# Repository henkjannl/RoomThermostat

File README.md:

# Roomthermostat

I wanted to create a room thermostat that can be controlled remotely ('honey, did you remember to switch off the heating?') but which also remains fully operational if internet connectivity is lost. Therefore it can be controlled through Telegram, but also via the hardware unit if WiFi is down. This is also useful since visitors may not want to use Telegram.

This fully (software & mechanics & electronics) open source project is based on an ESP32 microcontroller and the OpenTherm protocol.

The thermostat can be controlled by three touchbuttons on the device or via Telegram. 
In Telegram, an inline keyboard is used which changes depending on the context. This way, the user experience is similar to controlling the device via the hardware. The menu status of each Telegram user is kept in memory, so all users can communicate with the thermostat independently.

### Priorities for the temperature setpoint

The temperature setpoint can be chosen in four different ways, with increasing priority level:
1. The lowest priority level is the **normal week schedule**, which says which day type it is depending on the day of the week. 
    * There are four predefined day types:
        * :house_with_garden: **work from home**: temperature high at wake-up, and low at bed time
        * :office: **work from the office**: temperature high at wake up, low when going out, high when coming home and again low at bed time
        * :dancer: **weekend**, like :house_with_garden: **work from home** but with different wake-up and bed times
        * :palm_tree: **all day away**: temperature low throughout the day
    * The days of the week can be programmed in **settings**. 
    * All times for each type of day type can be modified
    * The low temperature and high temperature can be modified. These are the same temperatures for all day types
2. It is possible to **overrule multiple days** with a different day type, for instance to program multiple days as :dancer: **weekend day** (e.g. holiday at home) or as :palm_tree: **days away** (e.g. holiday away). 
    * The thermostat will be overruled until the number of days expires, or if the **overrule multiple days** function is **switched off** by the user
    * It is also possible to set the number of days to **forever**, for instance if heating is not required during the summer. The **overrule multiple days** can then be **switched off** in autumn.
3. **Today** and **tomorrow** can be overruled by a schedule that is different from the normal schedule.
    * Every night at midnight, **today** is replaced by **tomorrow** and **tomorrow** is switched off
    * Both can be **switched off** or changed by the user
    * For instance: if the holiday starts tomorrow, **multiple days** can be overruled to be :palm_tree: **day away**, after which **today** can be overruled as :dancer: **weekend day**
4. At all times, a **higher or lower temperature** can be manually selected. 
    * When the next programmed timeslot of the lower priority day type dawns, the temperature setting switches back the program of the nearest lower priority
    * It is also possible to choose ```Auto``` from the main menu in Telegram to switch the manual setpoint override off

If the temperature setpoint is manually overruled (priority level 4), it is displayed in red font.

Overruled day icons (priority levels 2 and 3) are surrounded by a red rectangle on the hardware unit. Telegram commands that overrule priority levels 2 and 3 will typically display  day type icons for the next 7 days.

The thermostat can be controlled by three touchbuttons on the device or via Telegram.
In Telegram, an inline keyboard is used which changes depending on the context. This way, the user experience is similar to controlling the device via the hardware. The menu status of each Telegram user is kept in memory, so all users can communicate with the thermostat independently.

## Controlling the thermostat through Telegram
### Main menu in Telegram

After selecting ```/start``` in Telegram, the following message and keyboard are returned:

The temperature in the room or settings of the thermostat can change over time. The display in Telegram is not automatically updated. The ```Status``` button can be used to update the status.

The settings menu has the following options:

### Simple use case in Telegram: going on a short holiday

The scenario is that we are going on a holiday for a few days and we will return on Monday.

To do this, select ```Overrule multiple days...``` in the main menu:

The icons in the next window show that the next two days are currently :office: **work from office**-days, followed by two :dancer: **weekend days** and again some :office: **work from office**-days.

Select :palm_tree:```All day away``` since we will be going on a holiday:

The :palm_tree:```All day away``` scenario means that the setpoint temperature will remain low throughout the day.

Then select ```4 days``` button multiple times in the next menu until the message says there are 5 :palm_tree:**all day away**-days, including Monday, which is the last day that the temperature should remain low:

Next select ```Back to the main menu```:

Now, the current day is also selected as an :palm_tree:**All day away**, with a low temperature setting for the remaining part of the day. To resolve this select ```Overrule today...```:

Choose :dancer:```Weekend day``` so we can pack our bags comfortably:

The remaining **Multiple days** will remain selected, only the current day will be overruled. It is also possible to overrule the next day while the remaining  **multiple days** remain overruled.

Of course it is also possible to do these steps after we leave, without the need to overrule the current day. As we are returning home during the next Saturday, we can also overrule the current day to ensure the house is comfortable upon arrival.

### Switch off the thermostat for a longer period of time

To switch off the thermostat for a longer period of time, for instance during the summer or during a long holiday, proceed as follows:
* Select ```Overrule multiple days...``` in the main menu
* Select :palm_tree: ```All day away```
* Select ```Forever```
* Select ```Back to the main menu...```

The thermostat is now switched off until ```Overrule multiple days``` is ```Switched off```

## Building the device

### Electronic hardware 
The hardware consists of:
* an ESP32 (mh-et-live-minikit-d1)
* an OpenTherm adaptor designed by Ihor Melnyk (DIYless Master OpenTherm Shield - https://diyless.com/product/master-opentherm-shield)
* a 2.4" 320x240 TFT screen (ILI9341)
* a 3D printed housing designed in FreeCad
* up to 4 Dallas DS18B20 temperature sensors
* a 4k7 resistor as pull-up for the Dallas temperature sensors
* 3 touch buttons (stainless steel screws, ISO7380-1, M5 x 16 + nut ISO4032 M5)
* 16 magnets (ø10 x 2.75 mm)
* a PCB designed in KiCad. This is optional, components can also be connected with wires, although it is more work and less reliable

Except for the housing and the OpenTherm interface, everything was ordered at AliExpress. The total bill of materials was about €35. The bill of materials can be found here ```\04 Electrical\Bill of materials.ods```.

### Mechanical hardware

There are two options:
* Connecting electronics via the cross connect PCB - the casing then consists of two panels, see ```03 Mechanical\RoomThermostat.FCStd```
* Connecting electronics via wires - the casing then consists of three panels, see ```03 Mechanical\RoomThermostat with PCB.FCStd```

In case of the PCB, there are two main parts to 3D print, a **front panel** and a **rear panel**. The rear panel can be screwed to the wall. The front panel is clicked on the rear panel through magnets.

Both prints need to be paused in some layer during printing to add round magnets before recommencing the printing.

It is possible to add up to four Dallas temperature sensors on the PCB (but fewer sensors should also work).

There are central ventilation openings on the bottom and top of the device to cool the ESP32 and prevent thermal cross talk between the heat of the ESP32 and the temperature sensors. There are ventilation openings in front of each temperature sensor also to measure the room temperature as accurate as possible.

The sofware has an **adjust sensor offset** feature to add or subtract a value from the measured temperature for calibration. That means that if the temperature measured by the thermostate is different from the actual room temperature, this can be corrected through the hardware buttons or via Telegram. 

### Software preparation
It is required to make a specific Telegram bot account for the thermostat. There are many sources explaining how a new Telegram bot can be created, such as in this [Random Nerd Tutorials Telegram example](https://randomnerdtutorials.com/telegram-control-esp32-esp8266-nodemcu-outputs/).

One ChatID can be provided to which the roomthermostat sends a message upon startup. This is useful to be aware that the thermostat was reset, due to a software bug or power outage.

In order to use the software, the user must first:
* make a copy of `template.jsn` (located in the `..\RoomThermoStat\05 Software\Roomthermostat\data` folder)
* rename the copy `config.jsn` 
* fill in details of one or more WiFi routers, including the timezone in which each router is located (`lon` and `lat` are currently not used)
* upload the data to SPIFFS using the ESP32 sketch upload data tool
* copy `User_Setup.h` and `User_Setup_Select.h` to the `..\Arduino\libraries\TFT_eSPI` folder (perhaps good to backup the existing versions)

The format of the `config.json` file is as follows:

```JSON
{
    "AccessPoints": [
        { "SSID": "SSIDOfWifi1", "password": "PasswordOfWifi1", "timezone" : "Europe/Amsterdam" },
        { "SSID": "SSIDOfWifi2", "password": "PasswordOfWifi2", "timezone" : "Europe/Amsterdam" }
    ],
    "BotName"     : "Name of the bot",
    "BotUsername" : "Username of the bot",
    "BotToken"    : "##########:XXXXXXXXXXXXXXXXXXXXXXXX",
    "ChatID"      : "########"
}
```

Note that there is a `config.json` and a The format of the `config_test.jsn`. The `config_test.jsn` is for test purposes, with a different bot token. It can be used for test purposes while the main thermostat bot remains accessible. To use the test bot, specify ```#define USE_TESTBOT true``` in `Roomthermostat.ino`.

Next it is necessary to upload the data folder to the ESP32 using `Tools` > `ESP32 Sketch Data Upload` in the Arduino IDE (see how this works at [Random Nerd Tutorials Telegram](https://randomnerdtutorials.com/install-esp32-filesystem-uploader-arduino-ide/).

Also, a number of libraries must be installed in Arduino:
* `ArduinoJSON` by Benoît Blanchon - https://arduinojson.org/
* `DallasTemperature` by Miles Burton - https://github.com/milesburton/Arduino-Temperature-Control-Library
* `JPEGDecoder` by Bodmer - https://github.com/Bodmer/JPEGDecoder
* `OpenTherm` by Ihor Melnyk - https://github.com/ihormelnyk/opentherm_library
* `TFT_eSPI` by Bodmer - https://github.com/Bodmer/TFT_eSPI
* `UniversalTelegram` by Brian Lough - https://github.com/witnessmenow/Universal-Arduino-Telegram-Bot

Big shout out to everyone for creating and maintaining these beautiful pieces of work!

## Software internals

### Overview of processes
| File               | Module                                                       |
|--------------------|--------------------------------------------------------------|
| Roomthermostat.ino | Initialization and main loop                                 |
| a_constants.h      | Defines, constants, data types                               |
| b_interfaces.h     | Queues and structs that connect the subsystems               |
| c_logger.h         | Datalogging (to be implemented)                              |
| d_keyboard.h       | Keyboard                                                     |
| e_menu.h           | Menu of hardware unit                                        |
| f_telegram.h       | Handler for Telegram messages                                |
| g_controller.h     | Temperature controller, including PID controller and program |
| h_temperature.h    | Temperature measurement and communication with boiler        |
| i_wifi_time.h      | Wifi controller and real time clock                          |
| j_jpeg.h           | Library to display jpeg images                               |
| k_display.h        | Display of the hardware unit                                 |
| l_backlight.h      | Backlight                                                    |

<br><br>

## Flow of events and messages

Initially, FreeRTOS was envisaged to handle all different processes. However, I did not (yet) get this working together with the OpenTherm library, which is very time critical. It is only possible to debug this with the live boiler attached,  which is a little barrier. Now, all processes are handled sequentially by the main loop.

It also appears that the SPI bus that communicates with the display does not work well while the capacitive touch button routine is called. Every time the display updates, the `touchRead()` is temporarily disabled.

The touch buttons are also disabled while OpenTherm communicates with the boiler.

<br>
The flow of events and messages is as follows:
<br>

* On the left hand side, the events that trigger activities are listed
* The circles represent code
* The arrows between the circles represent messages that are sent over the queues

### User presses key
* the ISR is running at about 30 Hz and is kept a small as possible. The capacitive sensors sometimes give a spike which only lasts one clock tick. Therefor, a key press is only considered valid if the key remains pressed for 2 subsequent samples. The ISR of the keyboard only sends a message to the menu, containing the key that was pressed. Subsequent actions are then carried out by the menu and other modules
* The capacitive sensor does not work well together with the SPI bus of the display, resulting in a crash of the microcontroller. Also, the keyboard ISR can interfere with the timing of the OpenThrem protocol. Therefore, polling the capacitive sensors is disabled during display or OpenTherm communication 
* the Backlight is controlled by the Display. In some cases, a button press does not result in a command to the controller (e.g., pressing the 'up'-button while the top menu item was already selected). In these cases, the backlight should also switch on. Therefore, the menu always sends a `cmdBacklightOn` command directly to the Backlight
* Telegram can take a few seconds to return. To improve responsivity of the keyboard, Telegram is temporarily disabled while the user is interacting with the keyboard. Telegram will be re-enabled as soon as the blacklight switches off.
* the first key press is only used to switch on the backlight. If the backlight is off while a key is pressed, the key is ignored and the backlight is woken up

### User enters a command in Telegram
* the status of the Telegram menu is stored independently for each individual ChatID, so each user can interact with Telegram independently of the other Telegram users and of the hardware unit
* some commands change the status of the controller (e.g., change a wake up time may cause a different setpoint for the boiler), others do not (e.g., moving to another screen in Telegram)
* only commands that change the status of the controller are sent to the controller, the other commands are directly forwarded to the Telegram queue that handles sending a response to the chat
* if the controller receives the command, it causes an update of the display which in turn switches on the backlight. This way, people in the room may notice that the setpoint was potentially changed and may act accordingly
* after the controller completes the action, the command is forwarded to the Telegram queue that returns the response to the user

### The timer for temperature measurement expires
* after the temperature is measured, the controller gets the chance to change the boiler setpoint, and a display update is triggered. This is done via a  `cmdSilentUpdate` command, which does not trigger the backlight: the change is only visible to the user if the backlight was already switched on

### The timer for the boiler expires
* as the timer expires, the controller is called to update the boiler setpoint
* the controller then forwards the `cmdBoilerSending` command to the screen which changes the boiler icon
* then, the screen again forwards the command to the temperature queue which triggers actual communication with the boiler
* finally, a `cmdSilentUpdate` command restores the boiler icon to the normal state

### Check WiFi and time timer expires
* this event (re-)connects to WiFi if needed, syncs with the timeserver if needed and updates the screen to reflect the change of the icon, without switching on the backlight

### Backlight timer expires
* the backlight is switched off
* the menu of the hardware unit is flipped back to the home screen
* Telegram is re-enabled

## Overview of directories:
* GUI and icons were created in Inkscape and are located in `..\RoomThermoStat\02 User interface\GUI design.svg`
* All types and structures of the menu structure are managed in `..\RoomThermoStat\02 User interface\Menu structure.xlsx`
* GUI colors are chosen in Inkscape converted to RGB565 in  `..\RoomThermoStat\02 User interface\Color converter RGB565.xlsx`
* Mechanical design is done in FreeCAD and is located in `..\RoomThermoStat\03 Mechanical\_RoomThermostat.FCStd`
* The interconnect PCB is designed in KiCAD and is located in  `..\RoomThermoStat\04 Electrical\Interconnect PCB V1.0 - as ordered JLC PCB`
* Arduino programs to test individual pieces of hardware are located in `..\RoomThermoStat\05 Software\Tests`
* Current version of the Arduino software is located in `..\RoomThermoStat\05 Software\Roomthermostat`

## Over the air software updates

After uploading the code over the COM port the first time, over the air updates are possible. However, during normal operation, the keyboard handler will interfere with the update process.
Therefore, first use Telegram to select ```Settings``` > ```Receive over the air update...```. The keyboard handler, the boiler and Telegram will 
be disabled for five minutes during which time boiler will switch off. 
During these five minutes, th blue LED on the back of the ESP32 will blink. During this time, choose the over the air port in Arduino (instead of the COM port) and upload the software over WiFi.

# To do

Software:
* over the air update still not working well
* over the air update does not display network port in Arduino IDE (perhaps call ArduinoOTA.handle() more often?)
  * while waiting for over the air software update, display message on screen
* improve responsiveness (keys and Telegram)
  * try to get FreeRTOS working again to improve performance of buttons and Telegram
    * perhaps Telegram can run on other core?
  * implement OpenTherm protocol in hardware timer in non-blocking way
* separate timers for blocking Telegram and backlight (backlight longer than blocking Telegram)
* include icons in the menu
* save logdata through WiFi connection 
  * Deta Base?
  * send logfile as attachment to Telegram
* much code can be simplified to remove structures that were used in previous attempts to get the code working
    * some userEventMessage_t constructs can be replaced with sendMessage() calls
    * some userEventMessage_t constructors may no longer be used
    * ...
* send automatic updates to last message of known clients every 15 minutes
  * also store list of chatIDs in permanent storage?
  * add functionality to whitelist or blacklist chatIDs?
* optimize heater control functionality
    * allow user to modify water temperature of heater and shower
    * check if D-action is implemented well in PID controller
    * take into account the weather in the control strategy
    * monitor the time it takes to heat the room in the morning, and compensate that by starting earlier or start with higher temperature
* also enable setting the time and date through hardware buttons if WiFi is unavailable
* display progress upon startup
* try if SPI frequency in TFT_eSPI can be set to higher value

Code cleanup:
* find replace action GoOut > Leave
* cleanup Serial.print
* check use of const in function calls
* cleanup the use of messages. Some fields may no longer be needed

Hardware:
* add a capacitor to prevent brownout of the ESP32 at startup
* little more space between adjacent boards
* more room for connector
* no two components at same location on either side of the main PCB (order of soldering doesn't matter, desoldering is possible)
* next step: integrate OpenTherm components and ESP32 components on main board

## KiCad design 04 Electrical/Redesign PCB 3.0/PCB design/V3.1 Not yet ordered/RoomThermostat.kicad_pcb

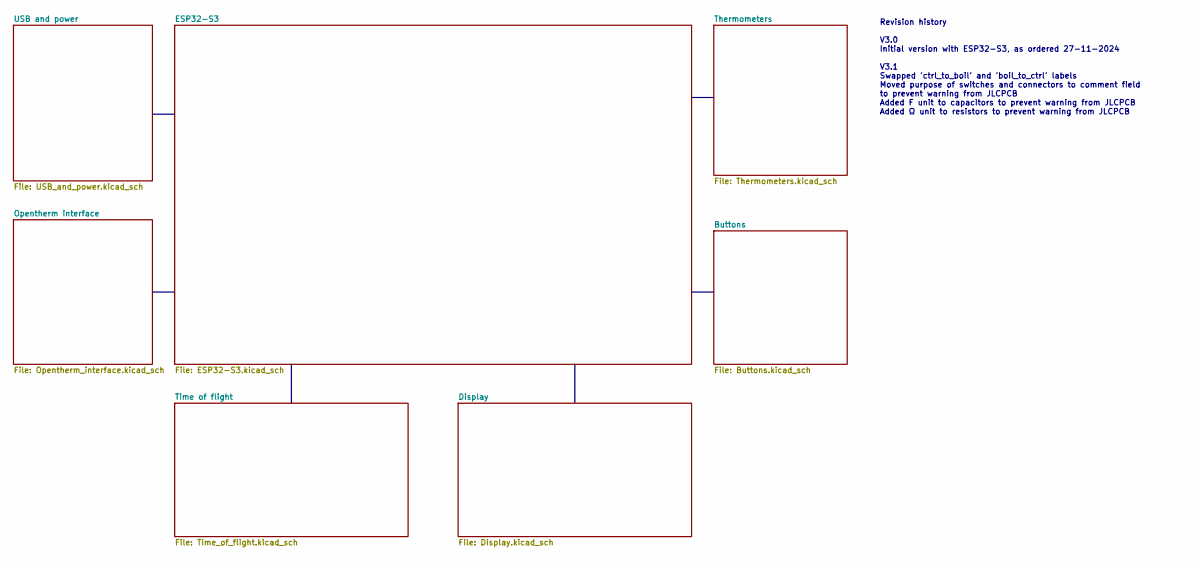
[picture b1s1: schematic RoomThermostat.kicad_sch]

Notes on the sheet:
Revision history V3.0 Initial version with ESP32-S3, as ordered 27-11-2024 V3.1 Swapped 'ctrl_to_boil' and 'boil_to_ctrl' labels Moved purpose of switches and connectors to comment field to prevent warning from JLCPCB Added F unit to capacitors to prevent warning from JLCPCB Added Ω unit to resisto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

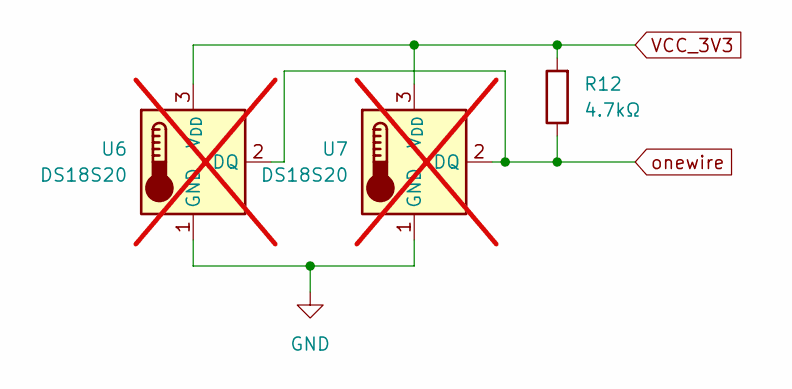
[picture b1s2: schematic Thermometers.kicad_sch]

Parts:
R12: 4.7kΩ; R_0603_1608Metric; LCSC Part # C23162
U6, U7: DS18S20; TO-92L_HandSolder; not fitted

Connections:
GND: U6.1 (GND), U7.1 (GND); also elsewhere on the board
VCC_3V3: R12.2, U6.3 (V_{DD}), U7.3 (V_{DD}); also elsewhere on the board
onewire: R12.1, U6.2 (DQ), U7.2 (DQ); also elsewhere on the board

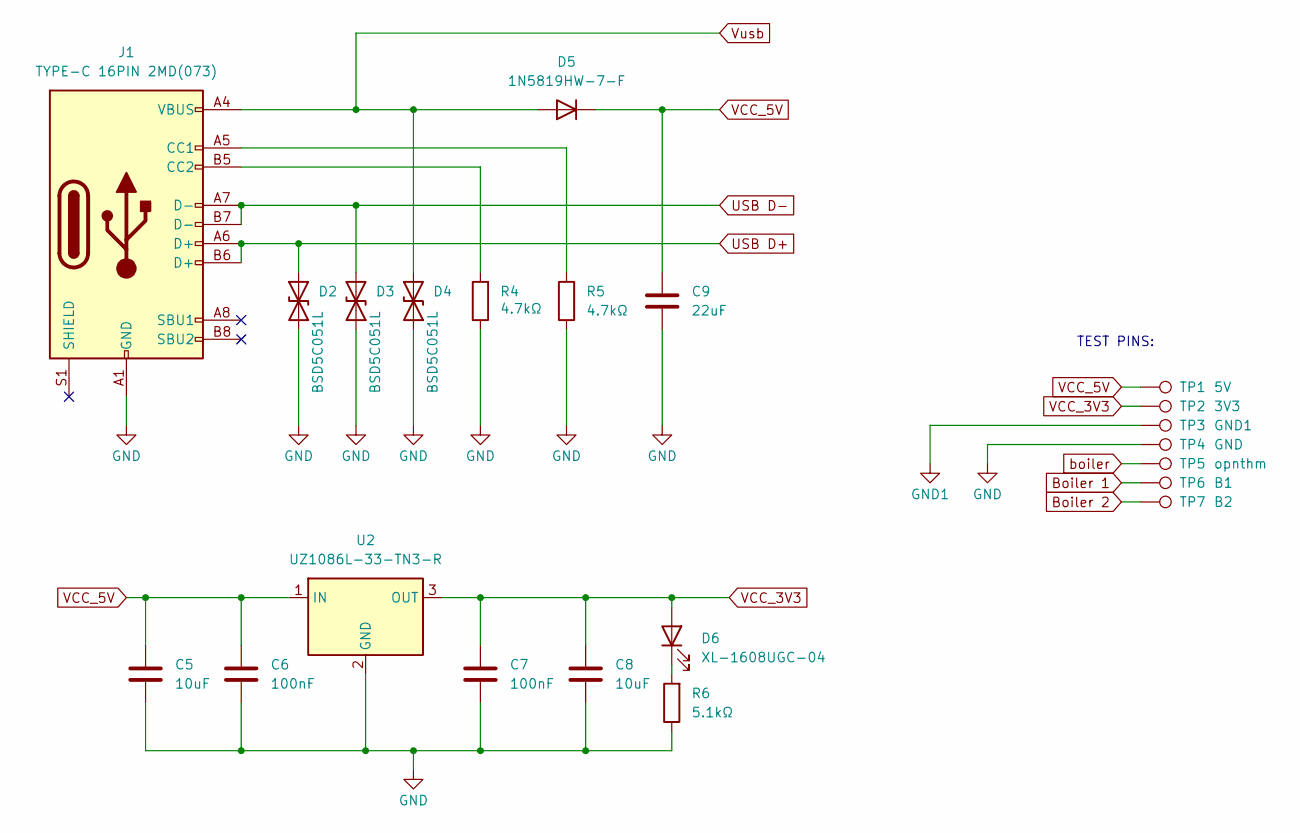
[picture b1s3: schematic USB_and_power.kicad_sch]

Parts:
C5, C8: 10uF; C_0402_1005Metric; LCSC Part # C15525
C6, C7: 100nF; C_0603_1608Metric; LCSC Part # C14663
C9: 22uF; C_0805_2012Metric; LCSC Part # C45783
D2, D3, D4: BSD5C051L; D_SOD-523; LCSC Part # C151983
D5: 1N5819HW-7-F; D_SOD-123; LCSC Part # C82544
D6: XL-1608UGC-04; LED_0603_1608Metric; LCSC Part # C965804
J1: TYPE-C 16PIN 2MD(073); USB_C_Receptacle_GCT_USB4105-xx-A_16P_TopMnt_Horizontal; LCSC Part # C2765186
R4, R5: 4.7kΩ; R_0603_1608Metric; LCSC Part # C23162
R6: 5.1kΩ; R_0603_1608Metric; LCSC Part # C23186
TP1: 5V; TestPoint_Keystone_5015_Micro-Minature; LCSC Part # C5199798
TP2: 3V3; TestPoint_Keystone_5015_Micro-Minature; LCSC Part # C5199798
TP3: GND1; TestPoint_Keystone_5015_Micro-Minature; LCSC Part # C5199798
TP4: GND; TestPoint_Keystone_5015_Micro-Minature; LCSC Part # C5199798
TP5: opnthm; TestPoint_Keystone_5015_Micro-Minature; LCSC Part # C5199798
TP6: B1; TestPoint_Keystone_5015_Micro-Minature; LCSC Part # C5199798
TP7: B2; TestPoint_Keystone_5015_Micro-Minature; LCSC Part # C5199798
U2: UZ1086L-33-TN3-R; TO-252-2; LCSC Part # C125862

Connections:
Boiler 1: TP6.1; also elsewhere on the board
Boiler 2: TP7.1; also elsewhere on the board
GND: C5.2, C6.2, C7.2, C8.2, C9.2, D2.1 (A1), D3.1 (A1), D4.1 (A1), J1.A1 (GND), J1.A12 (GND), J1.B1 (GND), J1.B12 (GND), R4.1, R5.1, R6.1, TP4.1, U2.2 (GND); also elsewhere on the board
GND1: TP3.1; also elsewhere on the board
unnamed: D6.1 (K), R6.2
unnamed: J1.A5 (CC1), R5.2
unnamed: J1.B5 (CC2), R4.2
USB D+: D2.2 (A2), J1.A6 (D+), J1.B6 (D+); also elsewhere on the board
USB D-: D3.2 (A2), J1.A7 (D-), J1.B7 (D-); also elsewhere on the board
VCC_3V3: C7.1, C8.1, D6.2 (A), TP2.1, U2.3 (OUT); also elsewhere on the board
VCC_5V: C5.1, C6.1, C9.1, D5.1 (K), TP1.1, U2.1 (IN)
Vusb: D4.2 (A2), D5.2 (A), J1.A4 (VBUS), J1.A9 (VBUS), J1.B4 (VBUS), J1.B9 (VBUS)
boiler: TP5.1; also elsewhere on the board

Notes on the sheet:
TEST PINS:

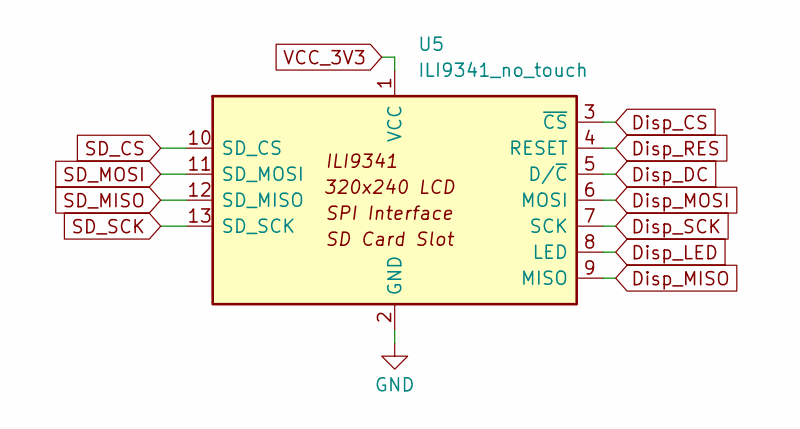
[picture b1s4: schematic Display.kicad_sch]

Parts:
U5: ILI9341_no_touch; ILI9341_no_touch_no_mount

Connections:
Disp_CS: U5.3 (~CS); also elsewhere on the board
Disp_DC: U5.5 (D/~C); also elsewhere on the board
Disp_LED: U5.8 (LED); also elsewhere on the board
Disp_MISO: U5.9 (MISO); also elsewhere on the board
Disp_MOSI: U5.6 (MOSI); also elsewhere on the board
Disp_RES: U5.4 (RESET); also elsewhere on the board
Disp_SCK: U5.7 (SCK); also elsewhere on the board
GND: U5.2 (GND); also elsewhere on the board
SD_CS: U5.10 (SD_CS); also elsewhere on the board
SD_MISO: U5.12 (SD_MISO); also elsewhere on the board
SD_MOSI: U5.11 (SD_MOSI); also elsewhere on the board
SD_SCK: U5.13 (SD_SCK); also elsewhere on the board
VCC_3V3: U5.1 (VCC); also elsewhere on the board

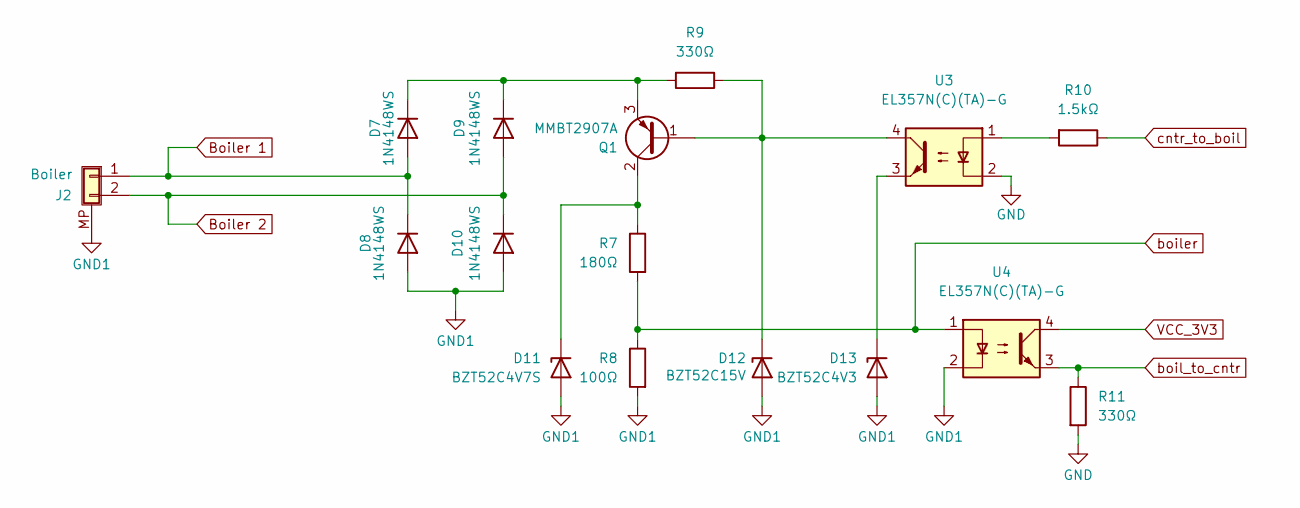
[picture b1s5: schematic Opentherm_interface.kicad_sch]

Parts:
D7, D8, D9, D10: 1N4148WS; D_SOD-323; LCSC Part # C2128
D11: BZT52C4V7S; D_SOD-323; LCSC Part # C5190168
D12: BZT52C15V; D_SOD-123; LCSC Part # C5299435
D13: BZT52C4V3; D_SOD-123; LCSC Part # C726993
J2: SM02B-SRSS-TB(LF)(SN); JST_SH_SM02B-SRSS-TB_1x02-1MP_P1.00mm_Horizontal; LCSC Part # C160402
Q1: MMBT2907A; SOT-23; LCSC Part # C916373
R7: 180Ω; R_0805_2012Metric; LCSC Part # C25270
R8: 100Ω; R_0805_2012Metric; LCSC Part # C17408
R9, R11: 330Ω; R_0805_2012Metric; LCSC Part # C17630
R10: 1.5kΩ; D_0805_2012Metric; LCSC Part # C4310
U3, U4: EL357N(C)(TA)-G; SO-4_4.4x3.6mm_P2.54mm; LCSC Part # C29981

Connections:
Boiler 1: D7.2 (A), D8.1 (K), J2.1; also elsewhere on the board
Boiler 2: D9.2 (A), D10.1 (K), J2.2; also elsewhere on the board
GND: R11.2, U3.2; also elsewhere on the board
GND1: D8.2 (A), D10.2 (A), D11.2 (A), D12.2 (A), D13.2 (A), J2.MP (Shield), R8.2, U4.2; also elsewhere on the board
unnamed: D7.1 (K), D9.1 (K), Q1.3 (E), R9.2
unnamed: D11.1 (K), Q1.2 (C), R7.1
unnamed: D12.1 (K), Q1.1 (B), R9.1, U3.4
unnamed: D13.1 (K), U3.3
unnamed: R10.2, U3.1
VCC_3V3: U4.4; also elsewhere on the board
boil_to_cntr: R11.1, U4.3; also elsewhere on the board
boiler: R7.2, R8.1, U4.1; also elsewhere on the board
cntr_to_boil: R10.1; also elsewhere on the board

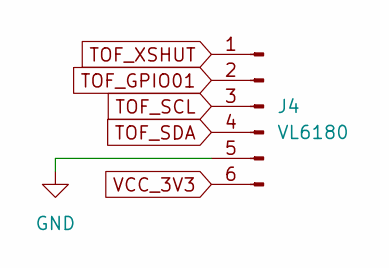
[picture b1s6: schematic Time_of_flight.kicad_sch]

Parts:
J4: VL6180; PinHeader_1x06_P2.00mm_Vertical

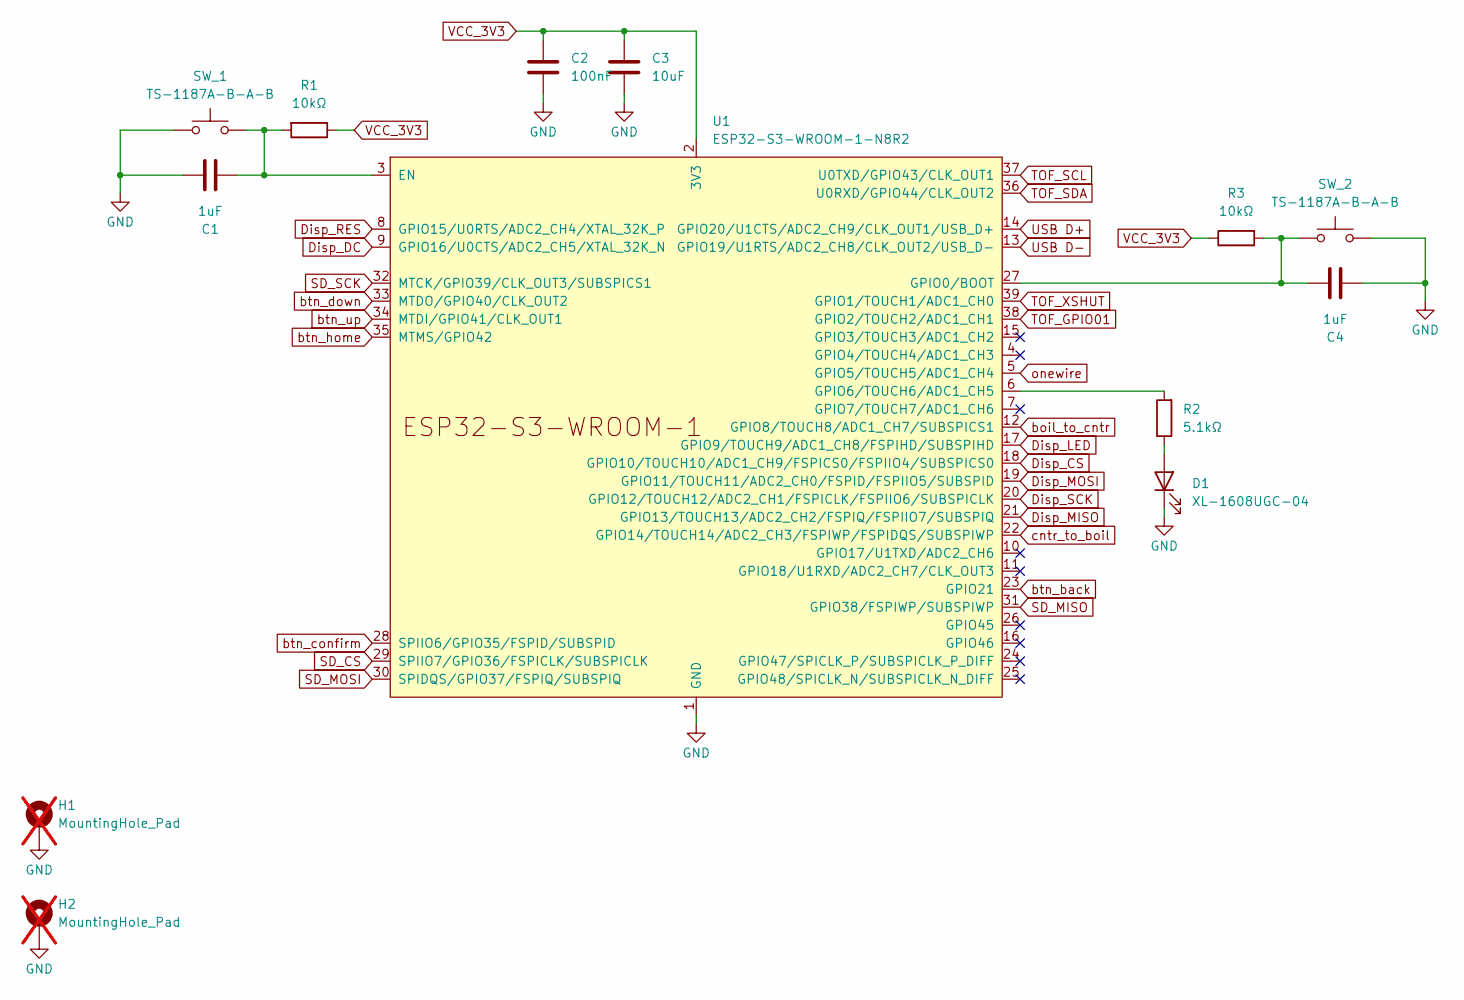
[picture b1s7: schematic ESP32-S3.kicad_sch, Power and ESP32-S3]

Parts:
C1, C4: 1uF; C_0603_1608Metric; LCSC Part # C15849
C2: 100nF; C_0603_1608Metric; LCSC Part # C14663
C3: 10uF; C_0402_1005Metric; LCSC Part # C15525
D1: XL-1608UGC-04; LED_0603_1608Metric; LCSC Part # C965804
H1, H2: MountingHole_Pad; MountingHole_3.2mm_M3_ISO7380_Pad_TopBottom; not fitted
R1, R3: 10kΩ; R_0603_1608Metric; LCSC Part # C25804
R2: 5.1kΩ; R_0603_1608Metric; LCSC Part # C23186
SW_1, SW_2: TS-1187A-B-A-B; SW_SPST_TL3342; LCSC Part # C318884
U1: ESP32-S3-WROOM-1-N8R2; ESP32-S3-WROOM-1; LCSC Part # C2913204

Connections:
Disp_CS: U1.18 (GPIO10/TOUCH10/ADC1_CH9/FSPICS0/FSPIIO4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); also elsewhere on the board
Disp_DC: U1.9 (GPIO16/U0CTS/ADC2_CH5/XTAL_32K_N); also elsewhere on the board
Disp_LED: U1.17 (GPIO9/TOUCH9/ADC1_CH8/FSPIHD/SUBSPIHD); also elsewhere on the board
Disp_MISO: U1.21 (GPIO13/TOUCH13/ADC2_CH2/FSPIQ/FSPIIO7/S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); also elsewhere on the board
Disp_MOSI: U1.19 (GPIO11/TOUCH11/ADC2_CH0/FSPID/FSPIIO5/S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); also elsewhere on the board
Disp_RES: U1.8 (GPIO15/U0RTS/ADC2_CH4/XTAL_32K_P); also elsewhere on the board
Disp_SCK: U1.20 (GPIO12/TOUCH12/ADC2_CH1/FSPICLK/FSPIIO6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); also elsewhere on the board
GND: C1.2, C2.2, C3.2, C4.2, D1.1 (K), H1.1, H2.1, SW_1.2, SW_2.2, U1.1 (GND), U1.40 (GND), U1.41 (GND); also elsewhere on the board
unnamed: D1.2 (A), R2.1
unnamed: C1.1, R1.2, SW_1.1, U1.3 (EN)
unnamed: C4.1, R3.2, SW_2.1, U1.27 (GPIO0/BOOT)
unnamed: R2.2, U1.6 (GPIO6/TOUCH6/ADC1_CH5)
SD_CS: U1.29 (SPIIO7/GPIO36/FSPICLK/SUBSPICLK); also elsewhere on the board
SD_MISO: U1.31 (GPIO38/FSPIWP/SUBSPIWP); also elsewhere on the board
SD_MOSI: U1.30 (SPIDQS/GPIO37/FSPIQ/SUBSPIQ); also elsewhere on the board
SD_SCK: U1.32 (MTCK/GPIO39/CLK_OUT3/SUBSPICS1); also elsewhere on the board
TOF_GPIO01: U1.38 (GPIO2/TOUCH2/ADC1_CH1); also elsewhere on the board
TOF_SCL: U1.37 (U0TXD/GPIO43/CLK_OUT1); also elsewhere on the board
TOF_SDA: U1.36 (U0RXD/GPIO44/CLK_OUT2); also elsewhere on the board
TOF_XSHUT: U1.39 (GPIO1/TOUCH1/ADC1_CH0); also elsewhere on the board
USB D+: U1.14 (GPIO20/U1CTS/ADC2_CH9/CLK_OUT1/USB_D+); also elsewhere on the board
USB D-: U1.13 (GPIO19/U1RTS/ADC2_CH8/CLK_OUT2/USB_D-); also elsewhere on the board
VCC_3V3: C2.1, C3.1, R1.1, R3.1, U1.2 (3V3); also elsewhere on the board
boil_to_cntr: U1.12 (GPIO8/TOUCH8/ADC1_CH7/SUBSPICS1); also elsewhere on the board
btn_back: U1.23 (GPIO21); also elsewhere on the board
btn_confirm: U1.28 (SPIIO6/GPIO35/FSPID/SUBSPID); also elsewhere on the board
btn_down: U1.33 (MTDO/GPIO40/CLK_OUT2); also elsewhere on the board
btn_home: U1.35 (MTMS/GPIO42); also elsewhere on the board
btn_up: U1.34 (MTDI/GPIO41/CLK_OUT1); also elsewhere on the board
cntr_to_boil: U1.22 (GPIO14/TOUCH14/ADC2_CH3/FSPIWP/FSPIDQS/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); also elsewhere on the board
onewire: U1.5 (GPIO5/TOUCH5/ADC1_CH4); also elsewhere on the board

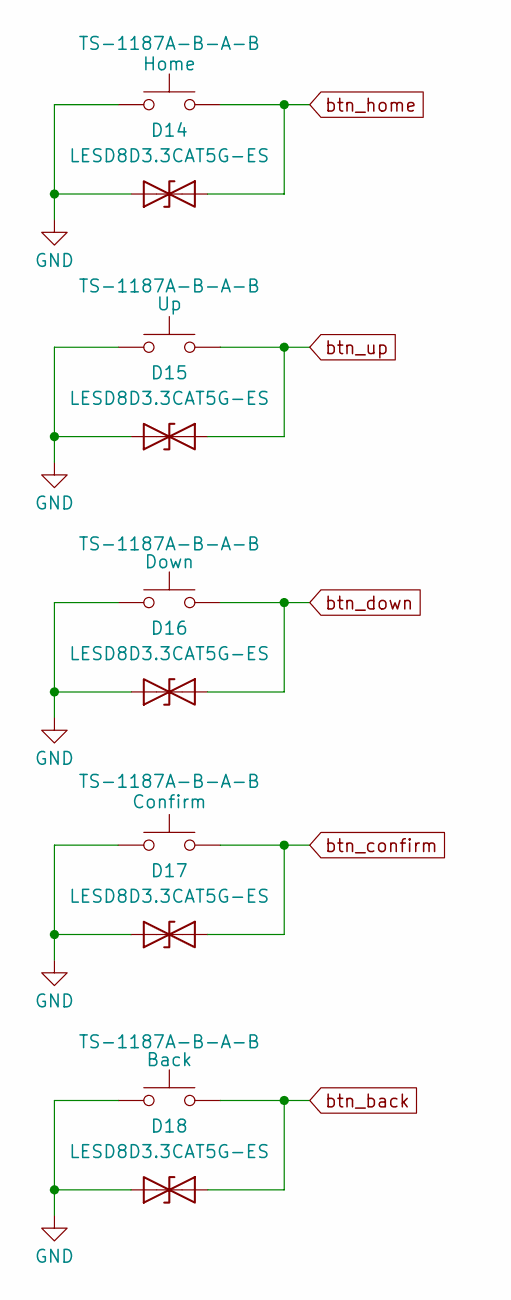
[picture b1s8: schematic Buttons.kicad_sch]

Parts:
D14, D15, D16, D17, D18: LESD8D3.3CAT5G-ES; D_SOD-882; LCSC Part # C5199186
SW_3, SW_4, SW_5, SW_6, SW_7: TS-1187A-B-A-B; SW_SPST_TL3342; LCSC Part # C318884

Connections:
GND: D14.1 (A1), D15.1 (A1), D16.1 (A1), D17.1 (A1), D18.1 (A1), SW_3.2, SW_4.2, SW_5.2, SW_6.2, SW_7.2; also elsewhere on the board
btn_back: D18.2 (A2), SW_7.1; also elsewhere on the board
btn_confirm: D17.2 (A2), SW_6.1; also elsewhere on the board
btn_down: D16.2 (A2), SW_5.1; also elsewhere on the board
btn_home: D14.2 (A2), SW_3.1; also elsewhere on the board
btn_up: D15.2 (A2), SW_4.1; also elsewhere on the board

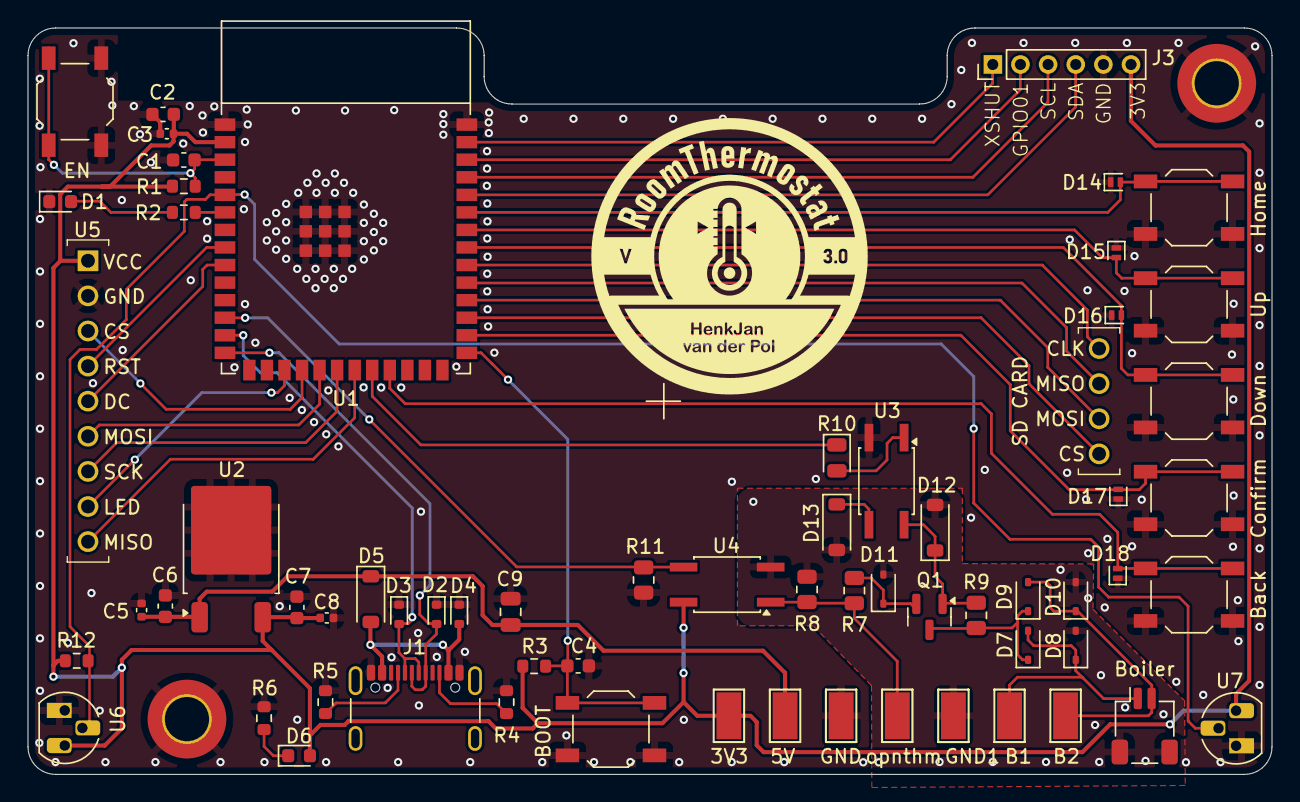
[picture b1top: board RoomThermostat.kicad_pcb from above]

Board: 2 copper layers, 90.0 x 54.0 mm, 66 parts (0 on the bottom side), 45 nets.

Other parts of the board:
J3: VL6180; PinHeader_1x06_P2.00mm_Vertical

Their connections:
GND: J3.5; also elsewhere on the board
TOF_GPIO01: J3.2; also elsewhere on the board
TOF_SCL: J3.3; also elsewhere on the board
TOF_SDA: J3.4; also elsewhere on the board
TOF_XSHUT: J3.1; also elsewhere on the board
VCC_3V3: J3.6; also elsewhere on the board

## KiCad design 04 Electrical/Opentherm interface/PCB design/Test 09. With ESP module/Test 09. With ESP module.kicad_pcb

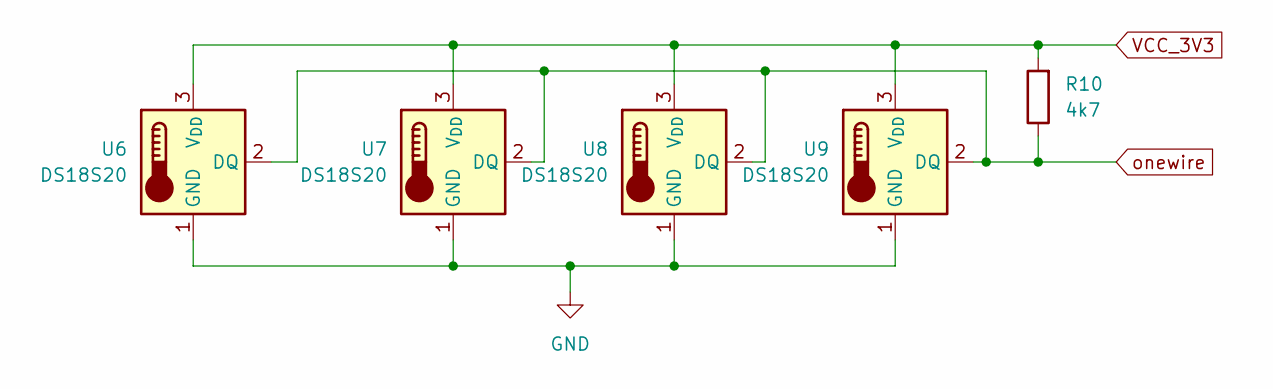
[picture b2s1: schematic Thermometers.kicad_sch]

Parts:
R10: 4k7; R_0201_0603Metric; LCSC Part # C23162
U6, U7, U8, U9: DS18S20; TO-92L_HandSolder

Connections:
GND: U6.1 (GND), U7.1 (GND), U8.1 (GND), U9.1 (GND); also elsewhere on the board
VCC_3V3: R10.2, U6.3 (V_{DD}), U7.3 (V_{DD}), U8.3 (V_{DD}), U9.3 (V_{DD}); also elsewhere on the board
onewire: R10.1, U6.2 (DQ), U7.2 (DQ), U8.2 (DQ), U9.2 (DQ); also elsewhere on the board

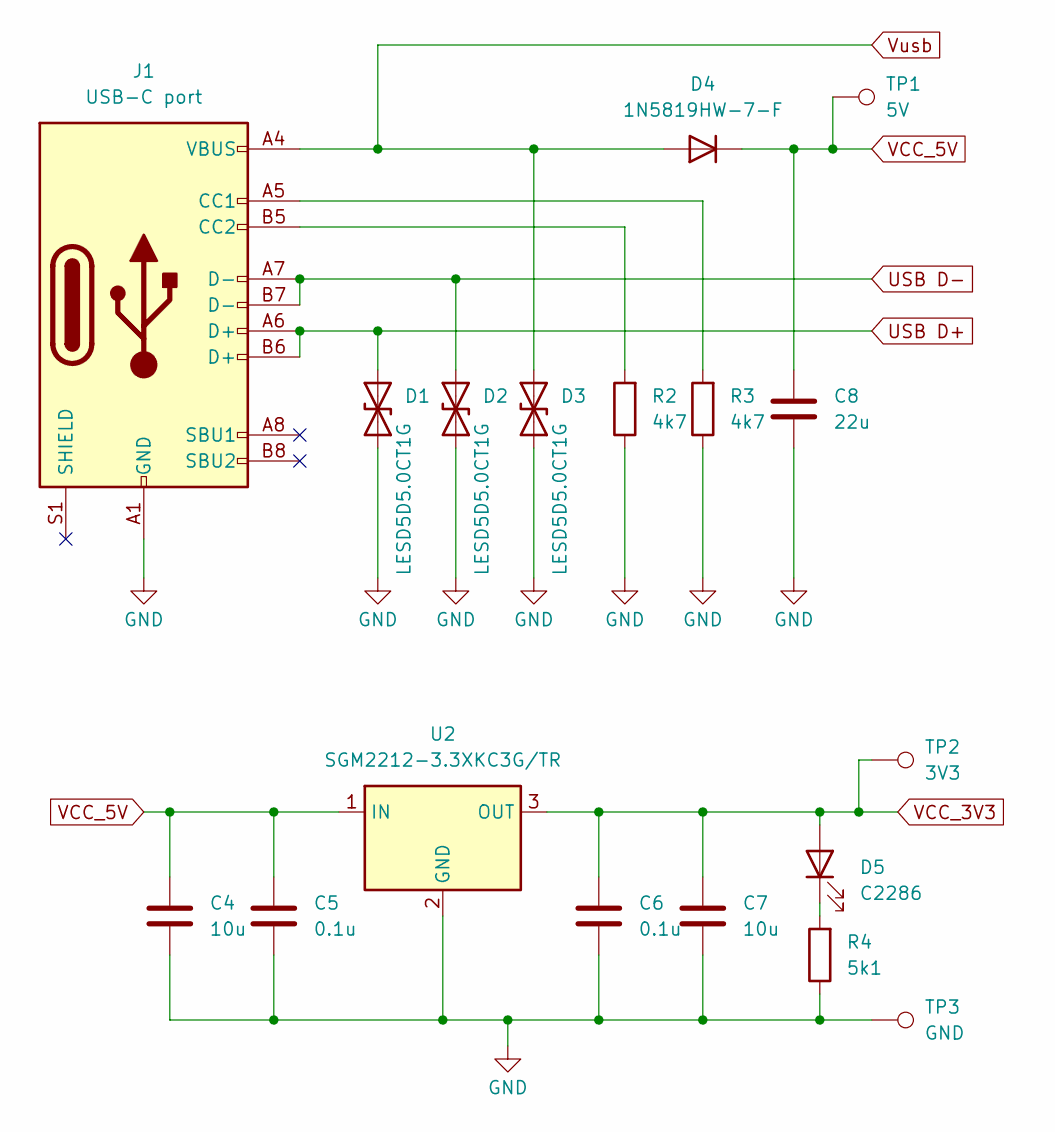
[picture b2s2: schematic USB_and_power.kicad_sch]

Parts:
C4, C7: 10u; C_0402_1005Metric; LCSC Part # C15525
C5, C6: 0.1u; C_0603_1608Metric; LCSC Part # C14663
C8: 22u; C_0805_2012Metric; LCSC Part # C45783
D1, D2, D3: LESD5D5.0CT1G; D_SOD-523; LCSC Part # C383211
D4: 1N5819HW-7-F; D_SOD-123; LCSC Part # C82544
D5: C2286; LED_0603_1608Metric; LCSC Part # C2286
J1: USB-C port; USB_C_Receptacle_GCT_USB4105-xx-A_16P_TopMnt_Horizontal; LCSC Part # C2765186
R2, R3: 4k7; R_0201_0603Metric; LCSC Part # C23162
R4: 5k1; R_0201_0603Metric; LCSC Part # C23186
TP1: 5V; TestPoint_Pad_D2.5mm
TP2: 3V3; TestPoint_Pad_D2.5mm
TP3: GND; TestPoint_Pad_D2.5mm
U2: SGM2212-3.3XKC3G/TR; SOT-223-3_TabPin2; LCSC Part # C3294699

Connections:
GND: C4.2, C5.2, C6.2, C7.2, C8.2, D1.1 (A1), D2.1 (A1), D3.1 (A1), J1.A1 (GND), J1.A12 (GND), J1.B1 (GND), J1.B12 (GND), R2.1, R3.1, R4.1, TP3.1, U2.2 (GND); also elsewhere on the board
unnamed: D5.1 (K), R4.2
unnamed: J1.A5 (CC1), R3.2
unnamed: J1.B5 (CC2), R2.2
USB D+: D1.2 (A2), J1.A6 (D+), J1.B6 (D+); also elsewhere on the board
USB D-: D2.2 (A2), J1.A7 (D-), J1.B7 (D-); also elsewhere on the board
VCC_3V3: C6.1, C7.1, D5.2 (A), TP2.1, U2.3 (OUT); also elsewhere on the board
VCC_5V: C4.1, C5.1, C8.1, D4.1 (K), TP1.1, U2.1 (IN); also elsewhere on the board
Vusb: D3.2 (A2), D4.2 (A), J1.A4 (VBUS), J1.A9 (VBUS), J1.B4 (VBUS), J1.B9 (VBUS)

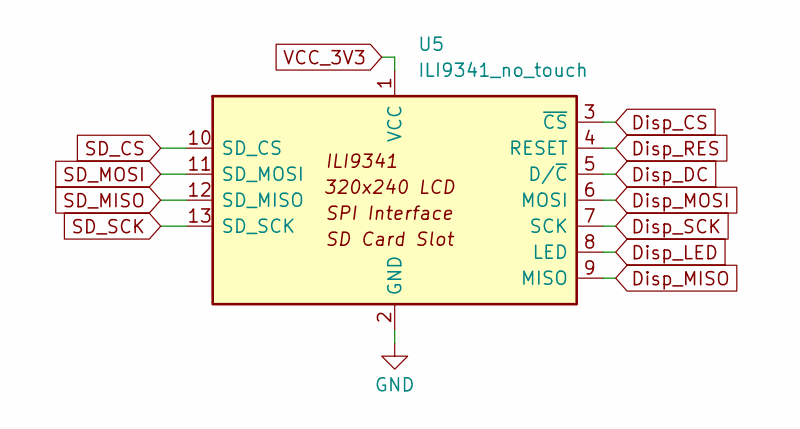
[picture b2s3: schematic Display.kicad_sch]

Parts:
U5: ILI9341_no_touch

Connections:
Disp_CS: U5.3 (~CS); also elsewhere on the board
Disp_DC: U5.5 (D/~C); also elsewhere on the board
Disp_LED: U5.8 (LED); also elsewhere on the board
Disp_MISO: U5.9 (MISO); also elsewhere on the board
Disp_MOSI: U5.6 (MOSI); also elsewhere on the board
Disp_RES: U5.4 (RESET); also elsewhere on the board
Disp_SCK: U5.7 (SCK); also elsewhere on the board
GND: U5.2 (GND); also elsewhere on the board
SD_CS: U5.10 (SD_CS); also elsewhere on the board
SD_MISO: U5.12 (SD_MISO); also elsewhere on the board
SD_MOSI: U5.11 (SD_MOSI); also elsewhere on the board
SD_SCK: U5.13 (SD_SCK); also elsewhere on the board
VCC_3V3: U5.1 (VCC); also elsewhere on the board

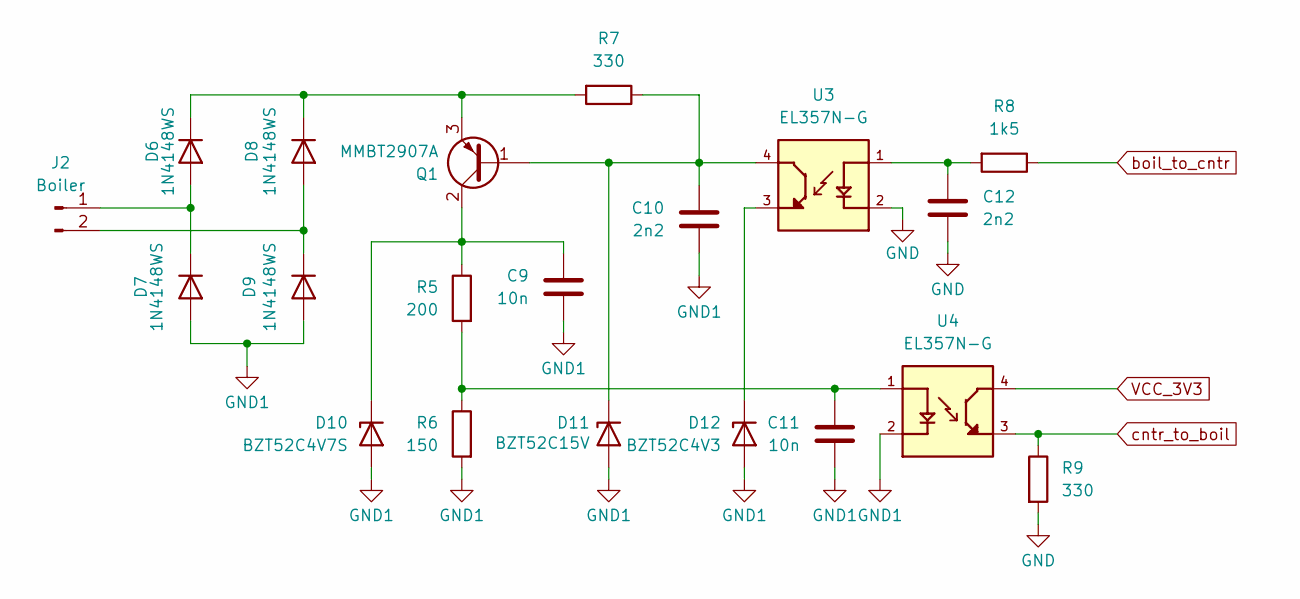
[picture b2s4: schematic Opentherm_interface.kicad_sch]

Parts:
C9, C11: 10n; C_0603_1608Metric; LCSC Part # C57112
C10, C12: 2n2; C_0603_1608Metric; LCSC Part # C1604
D6, D7, D8, D9: 1N4148WS; D_SOD-323; LCSC Part # C2128
D10: BZT52C4V7S; D_SOD-323; LCSC Part # C5190168
D11: BZT52C15V; D_SOD-123; LCSC Part # C5299435
D12: BZT52C4V3; D_SOD-123; LCSC Part # C726993
J2: Boiler; JST_SH_SM02B-SRSS-TB_1x02-1MP_P1.00mm_Horizontal; LCSC Part # C160402
Q1: MMBT2907A; SOT-23; LCSC Part # C916373
R5: 200; R_0805_2012Metric; LCSC Part # C25292
R6: 150; R_0805_2012Metric; LCSC Part # C17471
R7: 330; R_0805_2012Metric; LCSC Part # C17630
R8: 1k5; D_0805_2012Metric; LCSC Part # C4310
R9: 330; D_0805_2012Metric; LCSC Part # C17630
U3, U4: EL357N-G; OPTO_EL357N-G; PARTREV 6; LCSC Part # C29981

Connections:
GND: C12.1, R9.2, U3.2; also elsewhere on the board
GND1: C9.1, C10.2, C11.1, D7.2 (A), D9.2 (A), D10.2 (A), D11.2 (A), D12.2 (A), R6.2, U4.2
unnamed: C11.2, R5.2, R6.1, U4.1
unnamed: C12.2, R8.2, U3.1
unnamed: D6.2 (A), D7.1 (K), J2.1
unnamed: D6.1 (K), D8.1 (K), Q1.3 (E), R7.2
unnamed: D8.2 (A), D9.1 (K), J2.2
unnamed: C9.2, D10.1 (K), Q1.2 (C), R5.1
unnamed: C10.1, D11.1 (K), Q1.1 (B), R7.1, U3.4
unnamed: D12.1 (K), U3.3
VCC_3V3: U4.4; also elsewhere on the board
boil_to_cntr: R8.1; also elsewhere on the board
cntr_to_boil: R9.1, U4.3; also elsewhere on the board

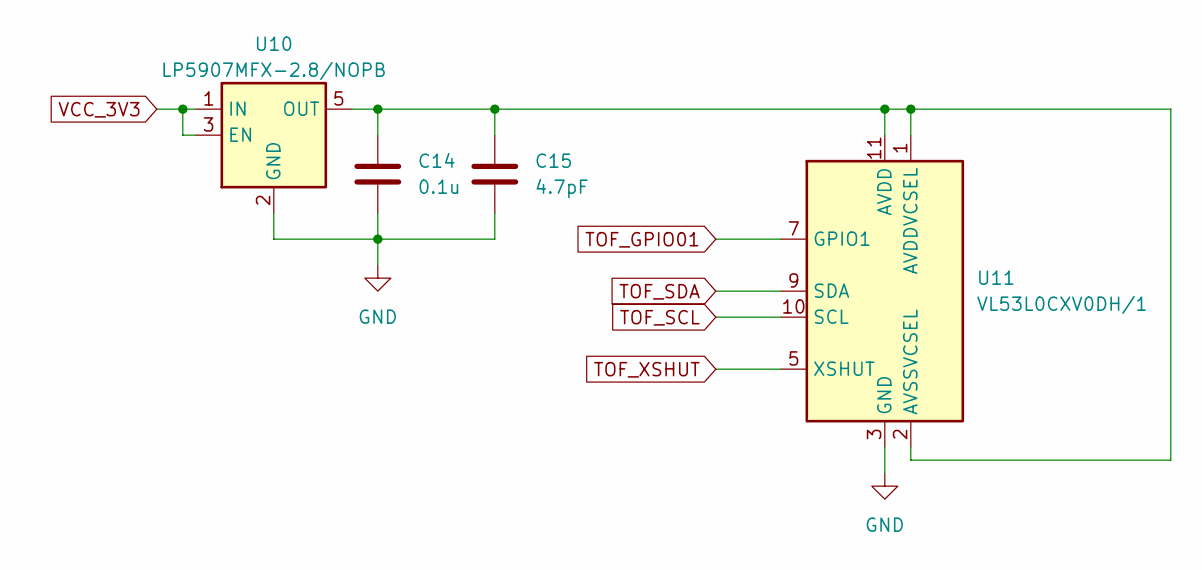
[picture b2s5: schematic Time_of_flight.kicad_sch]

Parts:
C14: 0.1u; C_0603_1608Metric; LCSC Part # C14663
C15: 4.7pF; C_0603_1608Metric; LCSC Part # C1669
U10: LP5907MFX-2.8/NOPB; SOT-23-5; LCSC Part # C186700
U11: VL53L0CXV0DH/1; ST_VL53L1x; LCSC Part # C91199

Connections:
GND: C14.2, C15.2, U10.2 (GND), U11.3 (GND), U11.4 (GND), U11.6 (GND), U11.12 (GND); also elsewhere on the board
unnamed: C14.1, C15.1, U10.5 (OUT), U11.1 (AVDDVCSEL), U11.2 (AVSSVCSEL), U11.11 (AVDD)
TOF_GPIO01: U11.7 (GPIO1); also elsewhere on the board
TOF_SCL: U11.10 (SCL); also elsewhere on the board
TOF_SDA: U11.9 (SDA); also elsewhere on the board
TOF_XSHUT: U11.5 (XSHUT); also elsewhere on the board
VCC_3V3: U10.1 (IN), U10.3 (EN); also elsewhere on the board
